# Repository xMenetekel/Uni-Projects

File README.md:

# Uni Projects

A collection of smaller university projects that don't warrant their own repository.
Each folder contains its own README with details, setup instructions, and results.

## Projects

| Project | Description | Tech | Runnable locally |
|---|---|---|---|
| [Binary Clock](binaryclock/) | Binary clock on a custom-made PCB | KiCad, C / Embedded | no (custom hardware) |
| [Protocol](protocol/) | Full-duplex protocol on the university PCB boards | C++ / Embedded | no (university lab only) |
| [Stardew Valley inspired Database](SQL/) | Database design and query exercises | SQL | yes (any SQL client) |
| [Paper: Dead Internet Theory](paper/) | Mini research paper | LaTeX / Markdown | no (document) |

## Notes
These projects were created during my studies and are kept here for reference. All of them predate my use of Git so this repository contains a curated
selection of the final results rather than a full commit history.
Some target specific hardware and are not runnable on standard machines -
see each folder's README for details.

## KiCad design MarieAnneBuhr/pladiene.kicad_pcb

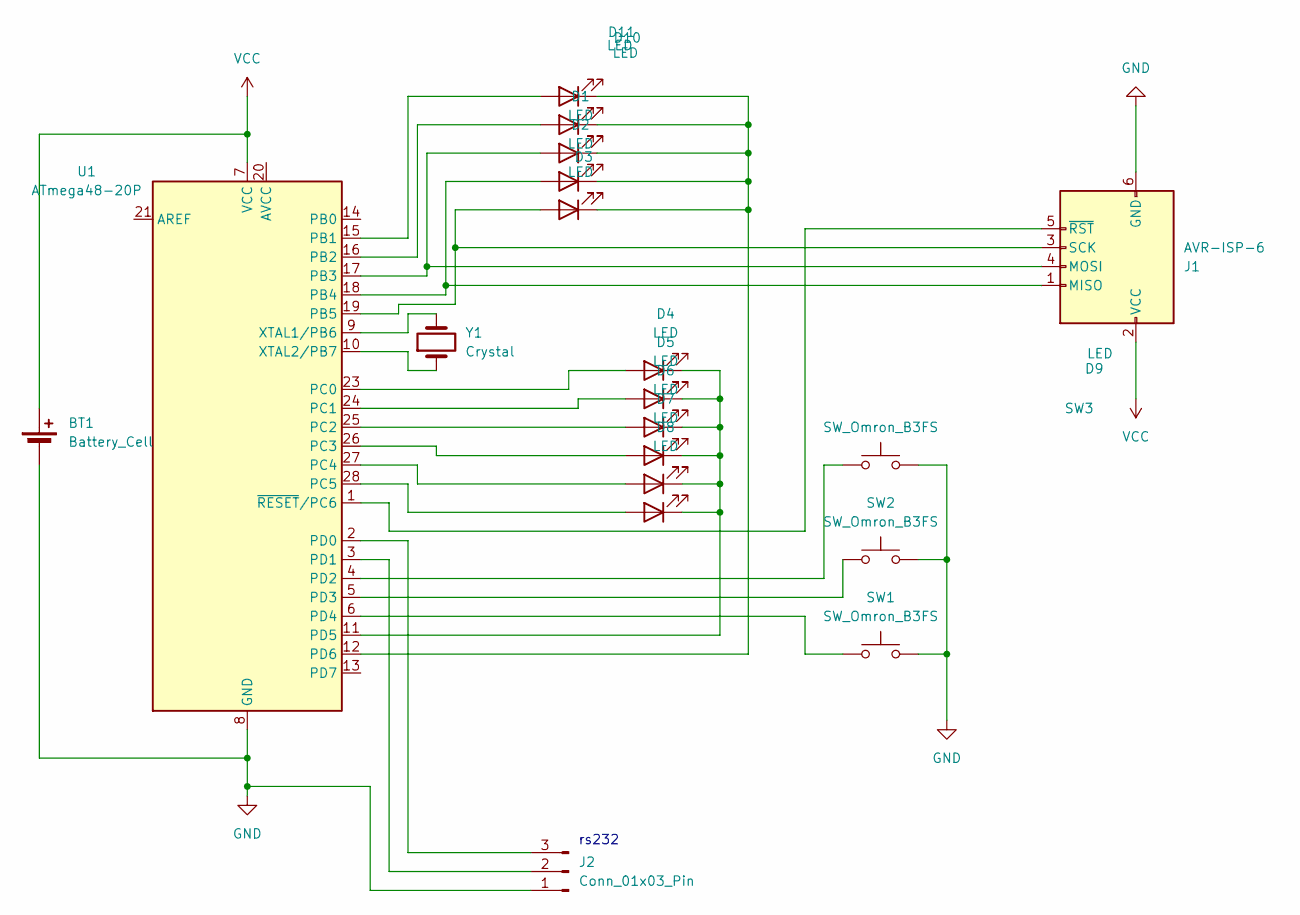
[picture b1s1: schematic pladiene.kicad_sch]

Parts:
BT1: Battery_Cell; BatteryHolder_Keystone_103_1x20mm
D1, D2, D3, D4, D5, D6, D7, D8, D9, D10, D11: LED; LED_D3.0mm
J1: AVR-ISP-6; IDC-Header_2x03_P2.54mm_Vertical
J2: Conn_01x03_Pin; FanPinHeader_1x03_P2.54mm_Vertical
SW1, SW2, SW3: SW_Omron_B3FS; SW_PUSH_6mm
U1: ATmega48-20P; DIP-28_W7.62mm
Y1: Crystal; Crystal_Round_D2.0mm_Vertical

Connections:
GND: BT1.2 (-), J1.6 (GND), J2.1, SW1.2, SW2.2, SW3.2, U1.8 (GND), U1.22 (GND)
unnamed: D1.2 (A), J1.4 (MOSI), U1.17 (PB3)
unnamed: D1.1 (K), D2.1 (K), D3.1 (K), D10.1 (K), D11.1 (K), U1.12 (PD6)
unnamed: D2.2 (A), J1.1 (MISO), U1.18 (PB4)
unnamed: D3.2 (A), J1.3 (SCK), U1.19 (PB5)
unnamed: D4.2 (A), U1.23 (PC0)
unnamed: D4.1 (K), D5.1 (K), D6.1 (K), D7.1 (K), D8.1 (K), D9.1 (K), U1.11 (PD5)
unnamed: D5.2 (A), U1.24 (PC1)
unnamed: D6.2 (A), U1.25 (PC2)
unnamed: D7.2 (A), U1.26 (PC3)
unnamed: D8.2 (A), U1.27 (PC4)
unnamed: D9.2 (A), U1.28 (PC5)
unnamed: D10.2 (A), U1.15 (PB1)
unnamed: D11.2 (A), U1.16 (PB2)
unnamed: J1.5 (~RST), U1.1 (~RESET/PC6)
unnamed: J2.2, U1.3 (PD1)
unnamed: J2.3, U1.2 (PD0)
unnamed: SW3.1, U1.4 (PD2)
unnamed: SW2.1, U1.5 (PD3)
unnamed: SW1.1, U1.6 (PD4)
unnamed: U1.9 (XTAL1/PB6), Y1.2
unnamed: U1.10 (XTAL2/PB7), Y1.1
VCC: BT1.1 (+), J1.2 (VCC), U1.7 (VCC)

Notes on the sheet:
rs232

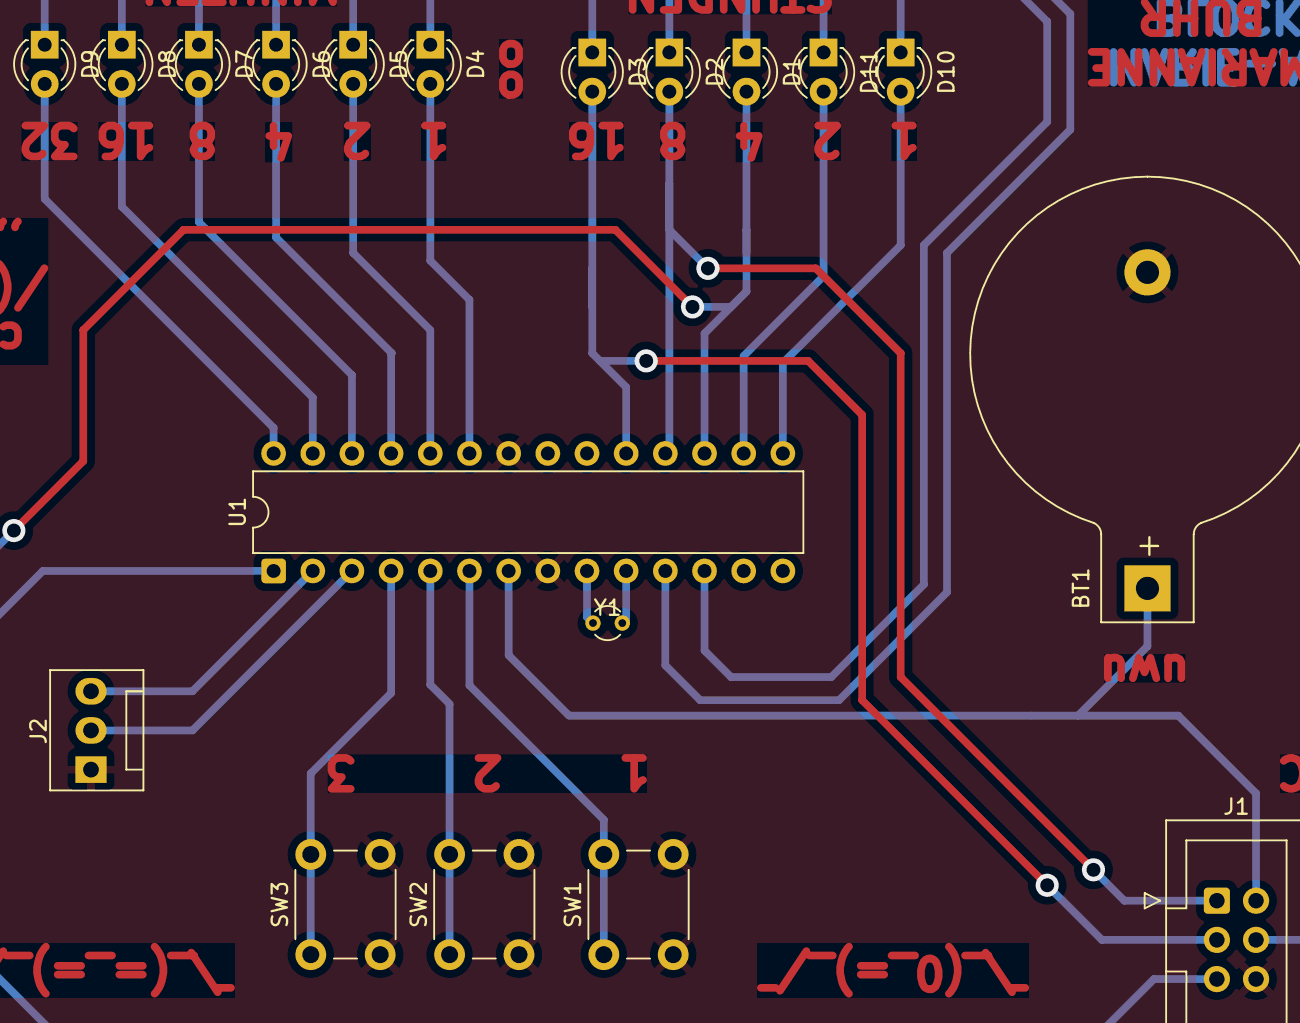
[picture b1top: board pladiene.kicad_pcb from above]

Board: 2 copper layers, 19 parts (0 on the bottom side), 23 nets.

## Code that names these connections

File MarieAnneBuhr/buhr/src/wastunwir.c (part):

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
[x] Uhrenquarz auf 60 Sekunden, dann zählt Minuten hoch
[x] Wenn 60 Minuten, dann zählt Stunden hoch + Minuten Reset
[x] Bei Stunden (Port B) PB6 aus dem Bitvektor?? entfernen, damit das nicht mitzählt, weil wir den nicht ansprechen
[x] Wenn Stunden auf 24 sind, dann auch Reset auf 0x00
[x] Uhrenquarz ordentlich ansprechen / Takt vorgibt, prescaler, Zeitbasis
[-] Sleepmode einbauen bzw optimierung stromverbrauch
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void main(){
    
    
    DDRD|=(0<<PD2)|(0<<PD3)|(0<<PD4);
    PORTD|=(1<<PD2)|(1<<PD3)|(1<<PD4);

    allesAn();

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	while(ASSR & (( 1 << TCN2UB) | (1 << TCR2BUB) | ( 1 << TCR2AUB))){} //wartet bis 3 flags null sind bevor weiter geht für synchrones arbeiten
    PWMWerteAn();
    TCCR0A|=(1<<WGM01)|(1<<WGM00);      //wgm01 und 00 sind die fastPWM einstellungen, timer zählt von 0 bis 255 und wdht dann
    TCCR0A|=(1<<COM0A1)|(1<<COM0A0);    //com0a1 / a0 steuert verhalten von OC0A / PD6, Set OC0A on compare match
    TCCR0A|=(1<<COM0B1)|(1<<COM0B0);    //com0b1 / b0 steuert verhalten von OC0B / PD5, Set OC0B on compare match
    TCCR0B |= (1<<CS01)|(1<<CS00);      //clk I/O/64 (from prescaler) für die pwm
    DDRD|=(1<<PD6);                     //PD 6 wird als ausgang gesetzt für data direction registry
    DDRD|=(1<<PD5);                     //PD 5 wird als ausgang gesetzt für data direction registry
    TIMSK2|=(1<<TOIE2);                 //setzt den timeroverflow interrupt
    EIMSK|=(1<<INT1);                   //Interrupt 1 wird aktiviert (Button 2)
    EIMSK|=(1<<INT0);                   //Interrupt 0 wird aktiviert (Button 3)
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                                        //Button 1
    EICRA|=(1<<ISC11)|(1<<ISC01);       //falling edge für beide buttons
    PCICR|=(1<<PCIE2);                  //setzt pinchange interrupt enable 
    PCMSK2|=(1<<PCINT20);               //Pin Change interrupt auf PD4 wird enabled
    
    SMCR|= (1<<SE);                     //macht sleepmode bit an aber glaube das hier halt sinnlos und das kann wahrscheinlicha uch unten stehen idk
    //set_sleep_mode(SLEEP_MODE_IDLE);
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}


status button1_nextState(status state){  //PD4, 6, PCINT20
    switch(state){
        case schlafmodus:    
            allesAn();   
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    }
}

status button2_nextState(status state){ //PD3, 
    switch(state){
        case schlafmodus:             
            return schlafmodus;
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    }
}

status button3_nextState(status state){ // PD2, 
    switch(state){
        case schlafmodus:             
            return schlafmodus;
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}

void allesAn(){
    DDRC|=(1<<PC5)|(1<<PC4)|(1<<PC3)|(1<<PC2)|(1<<PC1)|(1<<PC0);
    DDRB|=(1<<PB5)|(1<<PB4)|(1<<PB3)|(1<<PB2)|(1<<PB1);
}


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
